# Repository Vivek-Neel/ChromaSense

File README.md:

# ChromaSense

A wireless colorimeter I built for my M.Eng. project: a custom PCB around the TCS3530 colour sensor, an ESP32 that reads it and does the colour-science math, and a Python GUI that plots the result live on a CIE 1931 diagram. Parts cost works out to around €62 — commercial instruments that do roughly the same job run €1,500 to €6,000+.

If you only read one section, read [the three bugs](#three-bugs-that-didnt-look-like-bugs). That's where most of the actual engineering happened.

## What it does

Measures illuminance (lux), correlated colour temperature (CCT via McCamy's approximation), and CIE 1931 *xy* chromaticity, all live, streamed over Bluetooth to a desktop GUI at 10 Hz.

| | |
|---|---|
| Sensor | ams-OSRAM TCS35303-2M, 24-bit XYZ tristimulus |
| Board | 2-layer breakout I designed in KiCad, 25 × 30 mm — three built |
| MCU | M5Stack Core2 (ESP32), I²C @ 400 kHz |
| Link | Bluetooth SPP, JSON @ 10 Hz, commands back the other way |
| GUI | PyQt5, live CIE 1931 diagram |

Here it is live. The red dot is the measured chromaticity, moving between a warm source (~3,000 K) and a cool one (~11,000 K):

## How well it works

CCT checked against what standard illuminants say each scene should read. These numbers come from the field-calibration stage and were re-checked on the same scenes after the factory calibration went in:

| Scene | ChromaSense | Expected | Error |
|---|---|---|---|
| Overcast sky | 7098 K | ~7500 K (D75) | ~5% |
| Direct sun | 5852 K | ~5500 K (D55) | ~6% |
| Light cloud | 5492 K | ~5500 K | <1% |
| Warm LED, indoors | 3342 K | 3000–3500 K | ~1–5% |

Chromaticity repeats to roughly Δxy ±0.002–0.005 on broadband light. A multi-point comparison from about 5 lux to 116,000 lux — crossing a 32× gain switch — held a constant ratio against the reference the whole way, which is the result I cared about most: it means the response is linear across the full range and only one scale factor is left to pin down.

## Why there's a custom PCB at all

The TCS3530 runs on 1.8 V and comes in a 2.5 × 1.8 mm LGA package — you can't just dead-bug it onto a 3.3 V dev board, and an LGA gives you no visible joints to inspect after reflow, so the footprint has to be right first time. The breakout carries the sensor, its own LDO, decoupling caps, and a Grove connector that plugs straight into the Core2's I²C port.

| Ref | Part | Why |
|-----|------|-----|
| U1 | TCS35303-2M | the sensor |
| U2 | AP2112K-1.8TRG1 | 1.8 V LDO for the sensor |
| C4 | 1 µF 0402 MLCC | LDO input, 5 V side |
| C1, C2, C3 | 4.7 µF + 2 × 100 nF 0402 MLCC | 1.8 V rail: LDO output and sensor decoupling |
| J1 | Grove HY2.0-4P | I²C to the Core2 |

Full schematic: [`hardware/ChromaSense_Breakout_schematic.pdf`](hardware/ChromaSense_Breakout_schematic.pdf). There are no I²C pull-ups on the board, because the Core2's Grove port already provides them.

2-layer, DRC clean, fabbed at JLCPCB. I built three, and all three brought up and behaved identically — which turned out to matter later (see the Z-channel story).

## Firmware

PlatformIO, ESP32, M5Unified. The sensor driver (`firmware/lib/ChromaSense_TCS3530`) is mine, written from the datasheet and cross-checked against ams-OSRAM's reference driver. Every register in the header is cited to a datasheet page.

A few choices in there that weren't the default:

- **Hardware auto-gain is off.** The sensor can switch its own gain, but then the FIFO frame contents can change and the firmware can't be sure which gain a given reading was taken at. I moved gain switching into firmware instead: three steps (0.5×, 2×, 16×), stepping down above 800,000 counts and up below 3,000, with the gap between thresholds wider than the biggest gain step so it can't oscillate.
- **The first frame after a gain change gets thrown away.** It was integrated at the old gain. Using it gives one badly wrong reading at every transition, so the firmware waits one integration period and clears the FIFO first.
- **Only four channels go into the FIFO.** The sensor has eight; I disabled four of them, which fixes the frame at 12 bytes and removes a whole class of alignment bugs. Weeks later the factory calibration matrix arrived as 3×8 — and its last four columns were all zero for this sensor family. The frame I'd picked for safety was exactly what calibration needed.

**Calibration.** ams-OSRAM supplied factory calibration covering sixteen parts, one row per part, keyed by a 40-bit serial number burned into each sensor. So step one was a one-off firmware build to read five OTP registers, assemble the serial (557D0C06B8), and find the right row. Then three steps, in this order: normalise for integration time, normalise each channel's gain to a common 128× reference using the measured per-part correction, then a 3×4 matrix that maps raw counts to CIE XYZ.

The gain correction sounds fussy until you look at the numbers: on this part "2× gain" is actually 2.016× on Y and 1.992× on Z. Ignore that and you get a 1–2% channel-dependent error straight into chromaticity, and it changes with gain step, so you can't remove it later.

From XYZ it's arithmetic — x = X/(X+Y+Z), y = Y/(X+Y+Z), McCamy's cubic for CCT, calibrated Y for lux. McCamy is only valid near the blackbody curve, so anything outside 1500–20000 K comes back as 0 and the GUI shows a dash instead of a confident nonsense number.

The calibration numbers for this sensor are in `main.cpp` as plain constants — my supervisor's fine with that. What's not in here is ams-OSRAM's calibration file, their documentation, or their driver.

Also in there: an on-device dashboard, battery monitoring, and a dark mode that kills the backlight and status LED while the sensor keeps measuring — so the instrument isn't lighting up the thing it's measuring.

**How I built it up.** The whole signal chain — colour maths, display, Bluetooth, GUI — was built and tested against synthetic illuminants (D65, warm, cool) before a real sensor was connected. That paid off every time something broke later: with the maths already known good, a wrong reading had to be coming from the acquisition side.

## Three bugs that didn't look like bugs

None of these threw an error. In all three the system was doing exactly what its parts dictated, and the problem was an assumption I hadn't checked yet.

### 1. The driver that threw away a byte

The first library I used was a community one. Readings were plausible — they moved with the light, they saturated in bright sun — but colour accuracy was off, and I'd been blaming calibration. Reading ams-OSRAM's reference driver next to it showed why: the library read two bytes per channel, the sensor sends three. Every measurement was missing its bottom byte, a factor of 256 in resolution, with nothing to tell you.

I could have patched the read. I rewrote the driver instead, on the reasoning that a library that reads the wrong number of bytes has probably misunderstood the registers around it too. That was right — the rewrite turned up four more:

- **Everything read zero** during bring-up. The integration time was being written to the flicker-detection registers (0x8B/0x8C) instead of the ALS ones (0x87/0x88), so it stayed at its power-on default of ~355 µs instead of ~100 ms. The sensor was working perfectly and honestly reporting an absurdly short exposure.
- **Resolution still coarser than 24 bits**, even reading all three bytes correctly. `ALS_MSB_POSITION` has to be set explicitly, or the sensor truncates its own output before it ever reaches the FIFO. Same bug as the first one, one layer deeper — the first time the host was discarding data, this time the sensor never produced it. Having just found the first made the second recognisable.
- **Gain changes did nothing.** The library wrote gain to 0x50; the real gain registers are 0xC0–0xC3. The sensor sat at 2× whatever the firmware thought — which, it turned out, was also why my earlier lux calibration had been so hard to pin down.
- **Readings subtly wrong, health check passing anyway.** The oscillator has to be enabled and confirmed running before most registers work. But the ID register isn't clocked, so it answers regardless — and "read the ID, see if it matches" is exactly the check everyone uses to see if a sensor is alive.

### 2. The sky that read eight times too blue

Outdoors under overcast sky, Z (the blue channel) read about eight times higher than Y. For white light that ratio should be somewhere around 0.5–1.3.

My first guess was a PCB footprint error — sensor rotated 180°, putting the Z photodiode on the wrong side. But all three boards gave the same ratio (8.2, 8.6, 8.1), which ruled out anything to do with assembly. It was the sensor itself.

The TCS3530's Z photodiode is much more UV-sensitive than the CIE standard observer. Overcast sky is full of short-wavelength light scattered by the atmosphere, and the sensor sees it far more strongly than a human eye would. Under direct sun the same sensor read Z/Y ≈ 0.5. The measurement was real; my assumption that the sensor's raw response was close enough to the standard observer was what was wrong.

At the time I fixed it with two correction matrices — one for sky, one for sun — using the Z/Y ratio itself to pick between them, with hysteresis so sources near the boundary didn't flicker back and forth. That got CCT within about 5%. When the factory matrix arrived I deleted the whole scheme: its cross-channel terms correct the spectral mismatch directly, so one matrix handles both cases. Building the workaround taught me what the real fix needed to do; recognising it was redundant and removing it was the right call.

### 3. The backlight that wouldn't turn off

Dark mode needed the backlight off while the sensor kept running. The board library had documented calls for exactly that. I tried six approaches. Each failed differently: no effect, screen content blanked but light still on, a frozen screen, a register that read back as written but changed nothing — and one raw write that killed the backlight *and* the external I²C bus, so the sensor went down with it and the board needed a hard power cycle.

The failures weren't just unsuccessful, they were inconsistent with each other, which doesn't fit a software bug. It fits writing correct values to the wrong address space.

The clue was the colour of the status LED. The original Core2 has a green one and an AXP192 power-management chip. Mine has a blue one — that's the v1.1 revision, which uses an AXP2101, a different chip with a different register map. The library assumed AXP192 unconditionally. Every call I'd made was addressing the wrong chip's registers, which explained the whole pattern at once: some writes happened to land somewhere harmless, one landed on something important.

I checked that against M5Stack's own display-driver source and a long-running public issue before acting on it, then migrated the firmware to M5Unified, which detects the chip at boot. The calibration, driver, gain logic and telemetry format all carried over untouched — only the hardware layer underneath changed.

Six increasingly invasive register experiments, every one reasonable given the premise. The premise was what needed testing, and it took looking at an LED.

## The GUI

PyQt5 app: live chromaticity plot, telemetry panels for lux, CCT, raw 24-bit channel counts and battery, gain and saturation in the status bar, CSV logging.

**Putting live data on a picture.** The diagram background is a standard CIE 1931 reference image — it carries the wavelength ticks and colour-temperature labels people expect to read. But plotting a measured point on a raster image means knowing exactly where its pixels sit in CIE space. I picked three points on the spectral locus with known coordinates (380, 520 and 770 nm), fitted the pixel-to-CIE transform by least squares, and verified the origin independently with a reference mark.

To check the fit, I overlaid a spectral locus computed from the CIE colour-matching functions. It lined up on the top and right but drifted on the left flank around 480–510 nm, no matter how I adjusted the fit. The fit wasn't the problem — the image itself is about 12% wider per CIE unit horizontally than vertically (1420 vs 1263 px). Square in pixels, not square in CIE space. Stretching it to match would have distorted the baked-in labels, so the image stays as the display and the computed locus stays in the code as the way to re-verify it.

That computed locus had its own lesson: it looked faceted at the green apex. I assumed too few samples and went from 5 nm steps to 1 nm to 0.1 nm, and nothing changed — which was the useful result. `np.interp` is piecewise-linear; more samples just add more points along the same straight lines. `CubicSpline` fixed it by actually modelling the curve between data points.

Smaller things that mattered:

- **The device reports its own state.** Dark mode can be toggled from a button on the device or from the GUI. Instead of the GUI assuming what its last command did, every packet carries `"dark":0/1`, so the GUI always matches the device whichever side flipped it.
- **One bad packet can't crash it.** Early on I renamed a JSON field in firmware without updating the GUI and every packet crashed the dashboard. Now required keys are checked and malformed frames get dropped — and I treat the JSON format as an interface between two programs, not a detail.
- **Raw counts get logged**, not just the calibrated values, so if the calibration ever changes, old recordings can be reprocessed instead of re-measured.
- **10 Hz without stutter.** Qt re-parses a stylesheet every `setStyleSheet` call; with colour-graded labels at 10 Hz that adds up. Caching the last colour and skipping no-op updates fixed it. Bluetooth runs on its own `QThread` so a slow read never blocks the UI.

A typical packet:

```json
{"lux":417,"cct":4062,"x":0.3823,"y":0.3811,"X":112044,"Y":118631,"Z":80312,"gain":"2x","sat":0,"batt":87,"dark":0}
```

## Cost

| | € |
|---|---|
| TCS35303-2M | 8.50 |
| AP2112K-1.8TRG1 | 0.45 |
| Decoupling caps ×4 | 0.11 |
| Grove connector | 0.35 |
| PCB (JLCPCB, 5 off, shipped) | ≈3.00 |
| **Breakout total** | **≈12.40** |
| M5Stack Core2 | 50.00 |
| **Per unit** | **≈62.40** |

Full BOM with quantities and supplier links: [`BOM/ChromaSense_BOM_v2.xlsx`](BOM/ChromaSense_BOM_v2.xlsx).

For comparison, a [Sekonic C-800](https://galaxus.at/en/s1/product/sekonic-c-800-spectromaster-flash-unit-battery-flash-accessories-11488106) is €1,470, and a [Konica Minolta CL-200A](https://store.imatest.com/minolta-cl-200a-chroma-meter.html) is $6,500. To be clear, I'm not claiming this matches either — the C-800 is a real spectrometer with traceable calibration across the visible range, and this is one calibrated tristimulus sensor. What it does show is that you can get usable CIE coordinates for a small fraction of the cost if you're willing to build it yourself.

## What it doesn't do yet

- **Absolute lux isn't pinned down.** After calibration, Y is lux for the bare sensor. Anything placed over it — a housing, a window — will attenuate that, and the factor hasn't been measured yet. It's one number, `LUX_STACK_FACTOR` in `main.cpp`, and one afternoon with a reference meter once a housing exists. I didn't tune it to match a phone's light sensor in the meantime, because a phone isn't a reference.
- **Narrow-band sources fall outside the calibration.** Monitor primaries and saturated LEDs sit outside what the factory matrix was fitted for. That's inherent to tristimulus sensing — fixing it would need a spectrometer, not more tuning.
- **It's not traceable.** The calibration comes from ams-OSRAM's factory test equipment, but there's no DAkkS, NIST or PTB chain behind it. Good for relative and repeatable measurement, not for certification.
- **There's no enclosure.** I modelled a housing in Fusion 360 to the sensor's optical design constraints, but one connector position was never cross-checked against the PCB footprint, and with the deadline close I dropped it rather than print a part I hadn't verified. A wrong housing would have produced a worse, harder-to-spot error than no housing.
- **The calibration is for one sensor** (557D0C06B8). A different unit needs its own factory numbers from ams-OSRAM.

## Layout

```
chromasense/
├── hardware/     KiCad project, Gerbers, footprints, STEP model
├── firmware/     PlatformIO project
│   ├── src/main.cpp
│   └── lib/ChromaSense_TCS3530/   the driver
├── python-gui/   main_window.py, cie_widget.py, bt_worker.py
├── BOM/          full bill of materials
├── assets/
└── requirements.txt
```

## Running it

Firmware:
```bash
cd firmware
pio run --target upload
```
`platformio.ini` uploads on COM3 — change it to whatever your USB port is. If upload fails with `Invalid head of packet (0x7B)`, you're flashing the Bluetooth port by mistake: 0x7B is `{`, the start of the device's own JSON arriving where the bootloader expected a handshake.

Calibration for sensor 557D0C06B8 is already in `src/main.cpp`. Swap in your own sensor's numbers from ams-OSRAM if you're using a different unit.

GUI:
```bash
cd python-gui
pip install -r ../requirements.txt
python main_window.py
```
Pair the Core2 over Bluetooth, pick the right COM port in the dropdown, connect. Windows creates two Bluetooth COM ports when you pair; only one of them works.

## Licence

- **Code, docs, photos and BOM:** MIT — see [`LICENSE`](LICENSE).
- **Hardware design files** in `hardware/`: CERN Open Hardware Licence v2, Permissive — see [`hardware/LICENSE`](hardware/LICENSE).

Not covered by either:

- **`python-gui/cie_background.jpg`** is adapted from [*CIE-1931 diagram in LAB space*](https://commons.wikimedia.org/wiki/File:CIE-1931_diagram_in_LAB_space.svg) by Fuzzypeg, under [CC BY-SA 3.0](https://creativecommons.org/licenses/by-sa/3.0/). Details next to the file.
- **`python-gui/oth_logo.jpg`** is OTH Regensburg's logo, used to identify the institution. All rights remain with OTH Regensburg.
- **The calibration constants** in `firmware/src/main.cpp` are ams-OSRAM's per-sensor factory data, included with permission for this project. They aren't mine to license.
- ams-OSRAM, M5Stack and other product names are trademarks of their owners.

The GUI depends on PyQt5, which is GPL v3. That doesn't affect the licence of this source, but a bundled, distributed build of the GUI would fall under GPL terms.

---

M.Eng. Electrical and Microsystems Engineering, OTH Regensburg, Faculty ANK. Supervised by Prof. Johannes Wild. Graded 1.0.

**Vivek Wilson Neelamkavil** · [LinkedIn](https://www.linkedin.com/in/vivek-wilson/)

TCS3530 references throughout are to the public datasheet (ams-OSRAM DS001080 v3-00). No ams-OSRAM documentation, software, or raw calibration files are included here.

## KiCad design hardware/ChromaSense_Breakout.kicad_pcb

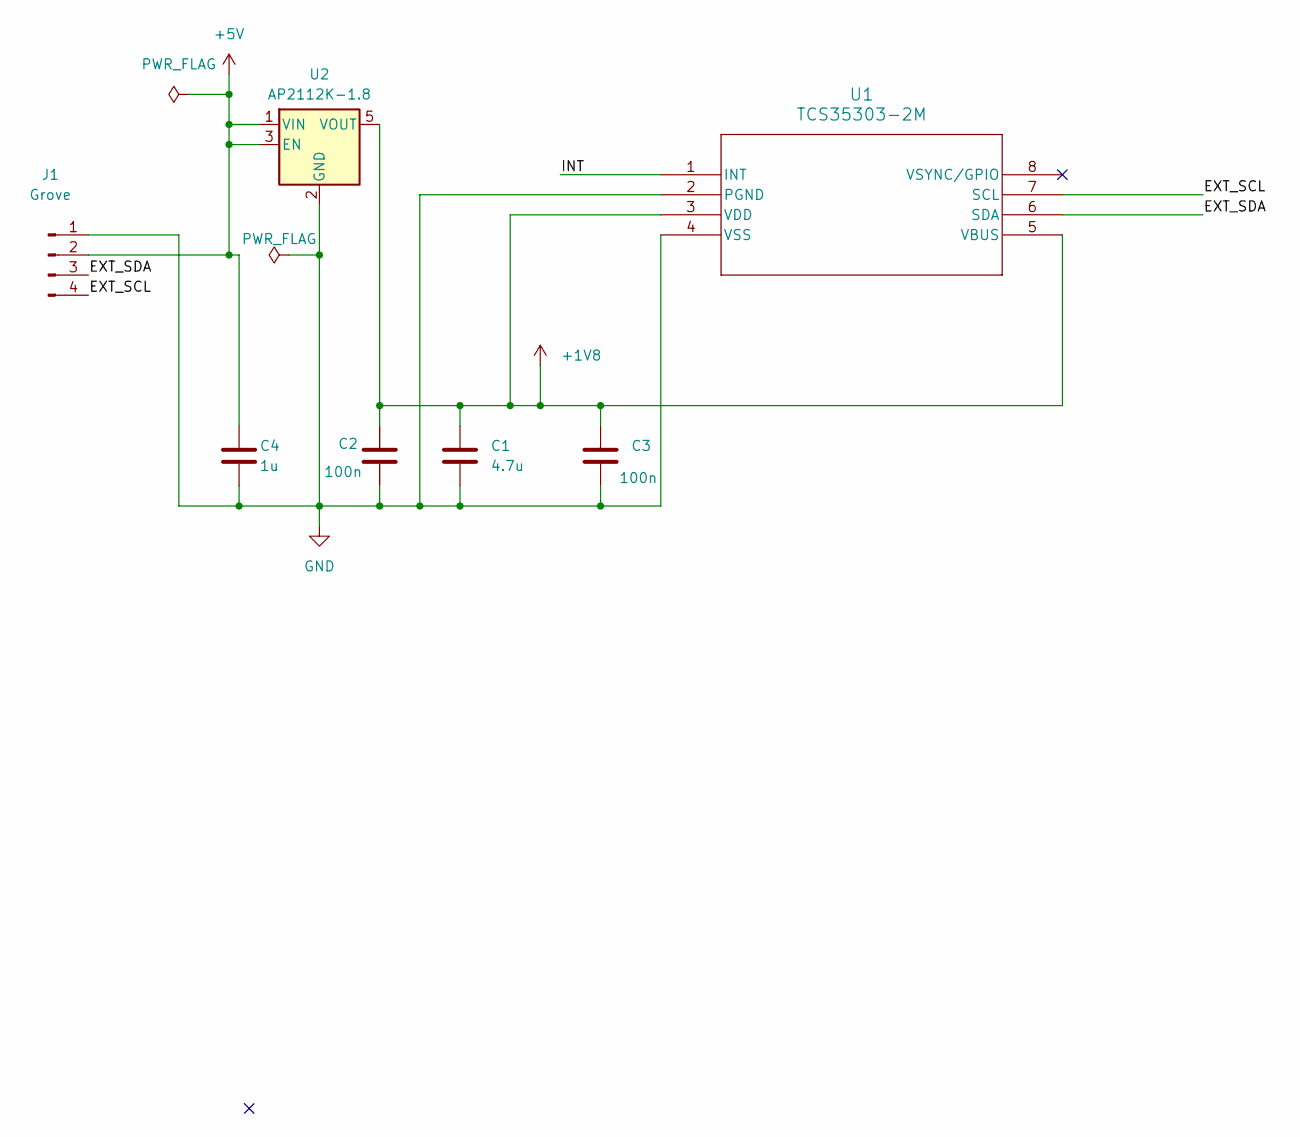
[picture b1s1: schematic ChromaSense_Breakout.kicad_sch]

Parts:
C1: 4.7u; C_0603_1608Metric
C2, C3: 100n; C_0603_1608Metric
C4: 1u; C_0603_1608Metric
J1: Grove
U1: TCS35303-2M; SMD8_TCS3530_OSM
U2: AP2112K-1.8; SOT-23-5

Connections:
+1V8: C1.2, C2.2, C3.1, U1.3 (VDD), U1.5 (VBUS), U2.5 (VOUT)
+5V: C4.1, J1.2, U2.1 (VIN), U2.3 (EN)
/EXT_SCL: J1.4, U1.7 (SCL)
/EXT_SDA: J1.3, U1.6 (SDA)
/INT: U1.1 (INT)
GND: C1.1, C2.1, C3.2, C4.2, J1.1, U1.2 (PGND), U1.4 (VSS), U2.2 (GND)

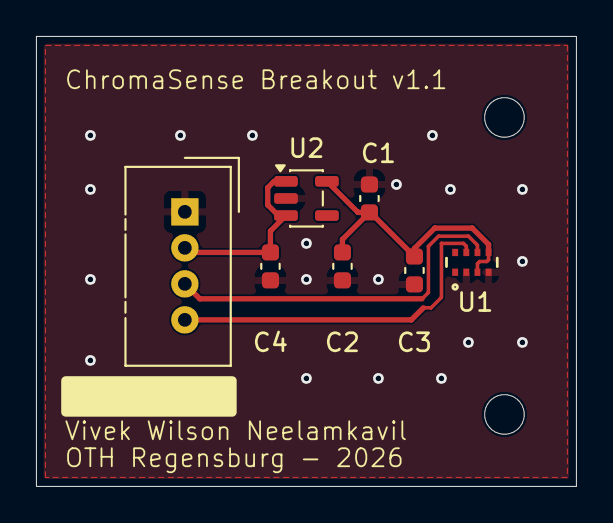
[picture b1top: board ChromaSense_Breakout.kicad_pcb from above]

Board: 2 copper layers, 30.0 x 25.0 mm, 7 parts (0 on the bottom side), 5 nets.

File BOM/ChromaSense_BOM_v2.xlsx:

ChromaSense — Bill of Materials
Project: Remote Color Sensor | OTH Regensburg — Faculty ANK | Supervisor: Prof.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
# | Component / Item | Part Number | Qty | Unit Price (€) | Total (€) | Supplier | Order Link 1 | Order Link 2 | Order Link 3
1 | Ams Osram TCS35303-2M XYZ Tristimulus Ambient Light Sensor IC | TCS35303-2M | 3 | 8.5 | 25.5 | Mouser / Digi-Key / Farnell | https://eu.mouser.com/ProductDetail/ams-OSRAM/TCS35303-2M?qs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 | https://ams-osram.com/de/products/sensor-solutions/ambient-l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 | https://de.farnell.com/en-DE/ams-osram-group/tcs35303-2m/col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
2 | AP2112K-1.8TRG1 1.8 V LDO Voltage Regulator (SOT-23-5) | AP2112K-1.8TRG1 | 2 | 0.45 | 0.9 | Mouser / Digi-Key / Farnell | https://eu.mouser.com/ProductDetail/Diodes-Incorporated/AP21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 | https://www.digikey.de/de/products/detail/diodes-incorporate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 | https://de.farnell.com/diodes-inc/ap2112k-1-8trg1/ldo-festsp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
3 | MLCC 4.7 µF / 10 V / X5R / 0402 Decoupling capacitor | GRM155R61A475ME15D | 10 | 0.06 | 0.6 | Mouser / Digi-Key / Reichelt | https://eu.mouser.com/ProductDetail/TAIYO-YUDEN/MLASL105BB54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 | https://www.reichelt.de/de/de/shop/produkt/mlcc_0402_4_7uf_1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 | https://de.farnell.com/multicomp-pro/0402x475k100ct/kondensa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
4 | MLCC 1 µF / 10 V / X5R / 0402 Decoupling capacitor | GRM155R61A105KE15D | 10 | 0.04 | 0.4 | Mouser / Digi-Key / Reichelt | https://eu.mouser.com/ProductDetail/KYOCERA-AVX/KGM05AR51A10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 | https://www.reichelt.de/de/de/shop/produkt/mlcc_0402_10uf_10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 | https://eu.mouser.com/ProductDetail/KYOCERA-AVX/KGM05AR51A10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
5 | Grove HY2.0-4P Connector I²C interface to M5Stack Core2 | HY2.0-4P (SMD) | 3 | 0.35 | 1.0499999999999998 | Eckstein / Berrybase / M5Stack | https://eckstein-shop.de/M5Stack-Grove-to-4-Pin-Connector-10pcs-EN | https://www.berrybase.de/m5stack-connector-grove-to-4-pin-10-stueck | https://docs.m5stack.com/en/module/extport_for_core2
ESTIMATED TOTAL (excl. shipping) |  |  |  |  | 28.45
